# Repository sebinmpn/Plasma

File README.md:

Welcome to our plasma diagnostic devices page.

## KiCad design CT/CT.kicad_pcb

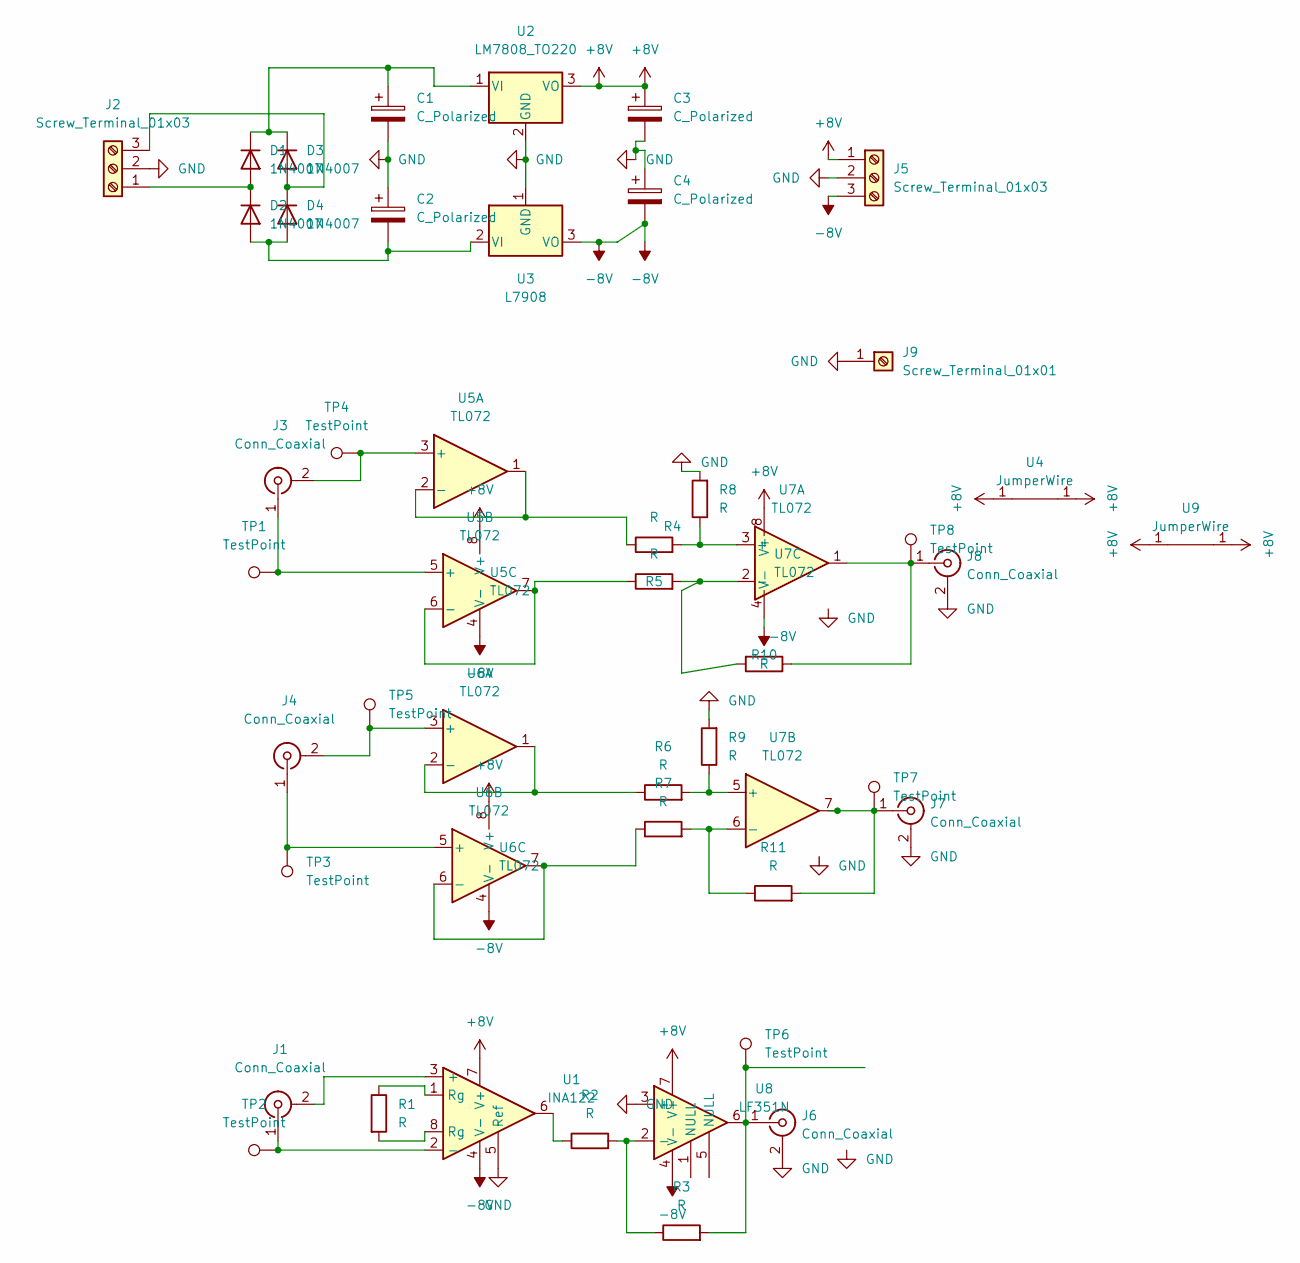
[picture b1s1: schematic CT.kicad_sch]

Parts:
C1, C2, C3, C4: C_Polarized; CP_Radial_D8.0mm_P3.50mm
D1, D2, D3, D4: 1N4007; D_DO-41_SOD81_P10.16mm_Horizontal
J1, J3, J4, J6, J7, J8: Conn_Coaxial; BNC_TEConnectivity_1478204_Vertical
J2, J5: Screw_Terminal_01x03; TerminalBlock_Phoenix_MKDS-1,5-3-5.08_1x03_P5.08mm_Horizont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
J9: Screw_Terminal_01x01; TestPoint_Loop_D2.54mm_Drill1.5mm_Beaded
R1, R2, R3, R4, R5, R6, R7, R8, R9: R; R_Axial_DIN0207_L6.3mm_D2.5mm_P7.62mm_Horizontal
R10, R11: R; R_0805_2012Metric_Pad1.20x1.40mm_HandSolder
TP1, TP2, TP3, TP4, TP5, TP6, TP7, TP8: TestPoint; PinHeader_1x01_P2.54mm_Vertical
U1: INA122; DIP-8_W7.62mm
U2: LM7808_TO220; TO-220-3_Vertical
U3: L7908; TO-220-3_Vertical
U4: JumperWire; JumperWire5
U5: TL072; DIP-8_W10.16mm_LongPads
U6, U7: TL072; DIP-8_W10.16mm
U8: LF351N; DIP-8_W10.16mm
U9: JumperWire; JumperWire6

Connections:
+8V: C3.1, J5.1, U1.7 (V+), U2.3 (VO), U4.1, U5.8 (V+), U6.8 (V+), U7.8 (V+), U8.7 (V+), U9.1
-8V: C4.2, J5.3, U1.4 (V-), U3.3 (VO), U5.4 (V-), U6.4 (V-), U7.4 (V-), U8.4 (V-)
GND: C1.2, C2.1, C3.2, C4.1, J2.2, J5.2, J6.2 (Ext), J7.2 (Ext), J8.2 (Ext), J9.1, R8.2, R9.2, U1.5 (Ref), U2.2 (GND), U3.1 (GND), U8.3 (+)
unnamed: C1.1, D1.1 (K), D3.1 (K), U2.1 (VI)
unnamed: C2.2, D2.2 (A), D4.2 (A), U3.2 (VI)
unnamed: D1.2 (A), D2.1 (K), J2.1
unnamed: D3.2 (A), D4.1 (K), J2.3
unnamed: J1.1 (In), TP2.1, U1.2 (-)
unnamed: J1.2 (Ext), U1.3 (+)
unnamed: J3.1 (In), TP1.1, U5.5 (+)
unnamed: J3.2 (Ext), TP4.1, U5.3 (+)
unnamed: J4.1 (In), TP3.1, U6.5 (+)
unnamed: J4.2 (Ext), TP5.1, U6.3 (+)
unnamed: J6.1 (In), R3.2, TP6.1, U8.6
unnamed: J7.1 (In), R11.2, TP7.1, U7.7
unnamed: J8.1 (In), R10.1, TP8.1, U7.1
unnamed: R1.1, U1.1 (Rg)
unnamed: R1.2, U1.8 (Rg)
unnamed: R2.1, U1.6
unnamed: R2.2, R3.1, U8.2 (-)
unnamed: R4.1, U5.1, U5.2 (-)
unnamed: R4.2, R8.1, U7.3 (+)
unnamed: R5.1, U5.6 (-), U5.7
unnamed: R6.1, U6.1, U6.2 (-)
unnamed: R6.2, R9.1, U7.5 (+)
unnamed: R7.1, U6.6 (-), U6.7
unnamed: R5.2, R10.2, U7.2 (-)
unnamed: R7.2, R11.1, U7.6 (-)

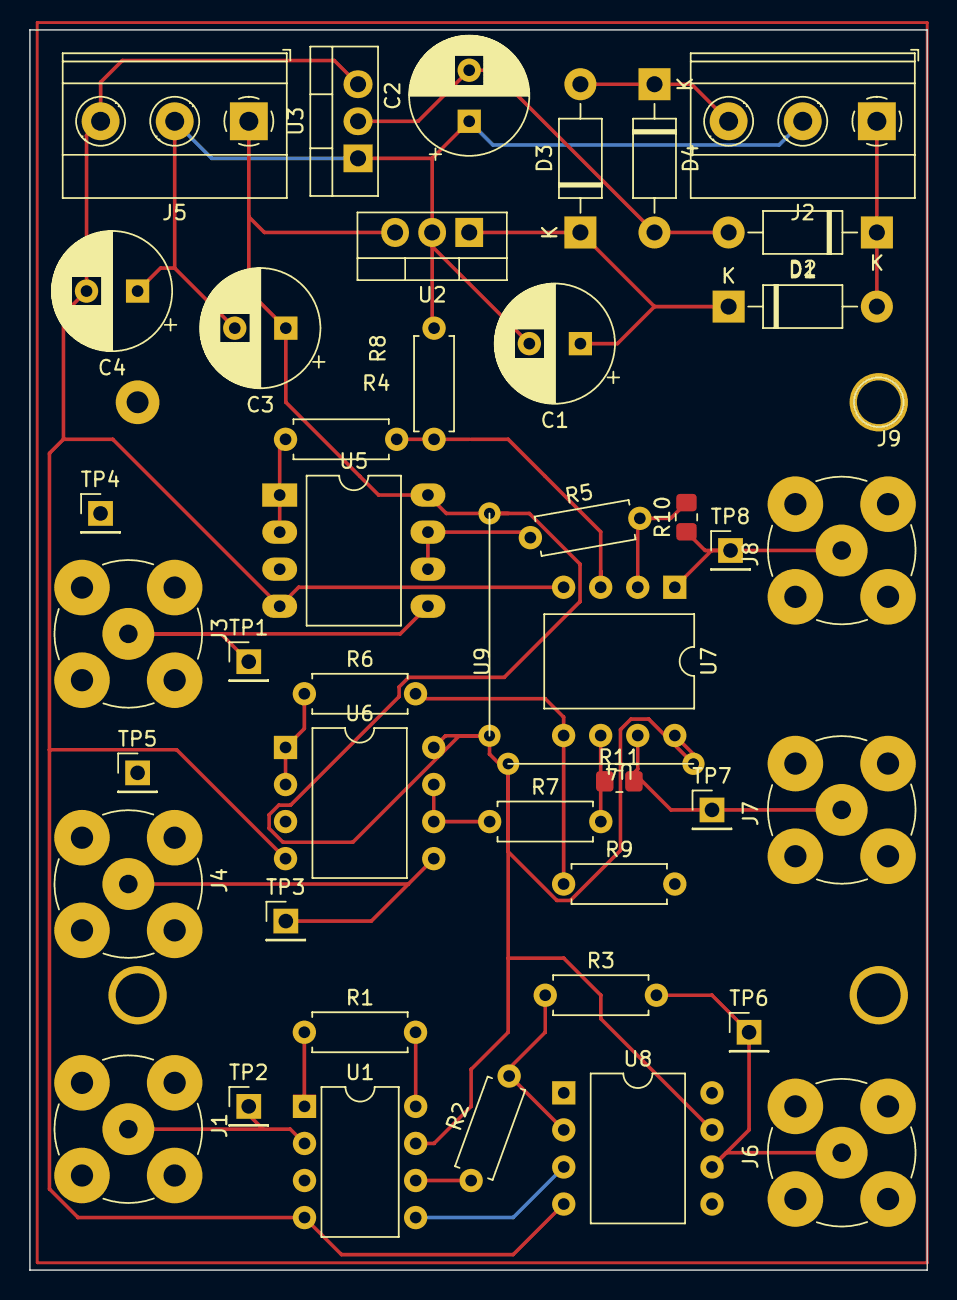
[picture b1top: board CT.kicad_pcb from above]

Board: 2 copper layers, 61.5 x 85.0 mm, 45 parts (0 on the bottom side), 28 nets.

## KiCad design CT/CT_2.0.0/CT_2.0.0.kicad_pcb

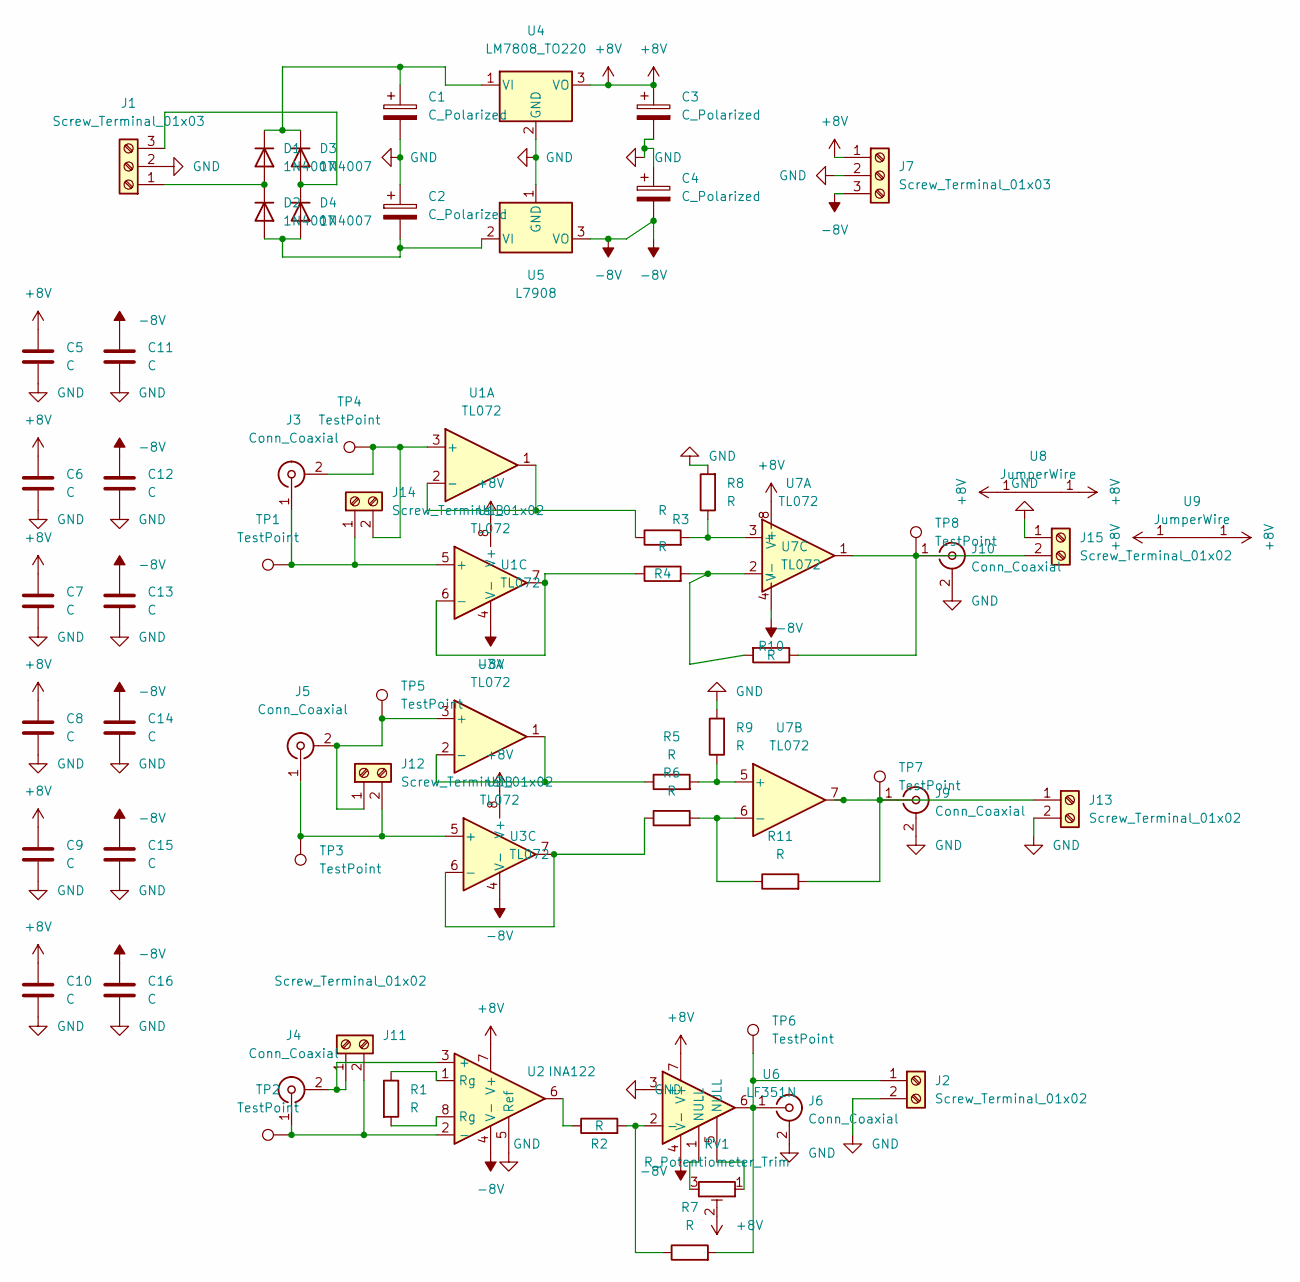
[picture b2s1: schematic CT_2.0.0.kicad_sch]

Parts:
C1, C2, C3, C4: C_Polarized; CP_Radial_D8.0mm_P3.50mm
C5, C6, C7, C8, C9, C10, C11, C12, C13, C14, C15, C16: C; CP_EIA-3528-21_Kemet-B_Pad1.50x2.35mm_HandSolder
D1, D2, D3, D4: 1N4007; D_DO-41_SOD81_P10.16mm_Horizontal
J1, J7: Screw_Terminal_01x03; TerminalBlock_Phoenix_MKDS-1,5-3-5.08_1x03_P5.08mm_Horizont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
J2, J11, J12, J13, J14, J15: Screw_Terminal_01x02; TerminalBlock_Phoenix_MKDS-1,5-2-5.08_1x02_P5.08mm_Horizont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
J3, J4, J5, J6, J9, J10: Conn_Coaxial; BNC_TEConnectivity_1478204_Vertical
R1, R2, R3, R4, R5, R6, R7, R8, R9: R; R_Axial_DIN0207_L6.3mm_D2.5mm_P7.62mm_Horizontal
R10, R11: R; R_0805_2012Metric_Pad1.20x1.40mm_HandSolder
RV1: R_Potentiometer_Trim; trimpot
TP1, TP2, TP3, TP4, TP5, TP6, TP7, TP8: TestPoint; PinHeader_1x01_P2.54mm_Vertical
U1: TL072; DIP-8_W10.16mm_LongPads
U2: INA122; DIP-8_W7.62mm
U3, U7: TL072; DIP-8_W10.16mm
U4: LM7808_TO220; TO-220-3_Vertical
U5: L7908; TO-220-3_Vertical
U6: LF351N; DIP-8_W10.16mm
U8: JumperWire; JumperWire5
U9: JumperWire; JumperWire6

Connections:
+8V: C3.1, C5.1, C6.1, C7.1, C8.1, C9.1, C10.1, J7.1, RV1.2, U1.8 (V+), U2.7 (V+), U3.8 (V+), U4.3 (VO), U6.7 (V+), U7.8 (V+), U8.1, U9.1
-8V: C4.2, C11.1, C12.1, C13.1, C14.1, C15.1, C16.1, J7.3, U1.4 (V-), U2.4 (V-), U3.4 (V-), U5.3 (VO), U6.4 (V-), U7.4 (V-)
GND: C1.2, C2.1, C3.2, C4.1, C5.2, C6.2, C7.2, C8.2, C9.2, C10.2, C11.2, C12.2, C13.2, C14.2, C15.2, C16.2, J1.2, J2.2, J6.2 (Ext), J7.2, J9.2 (Ext), J10.2 (Ext), J13.2, J15.1, R8.2, R9.2, U2.5 (Ref), U4.2 (GND), U5.1 (GND), U6.3 (+)
unnamed: C1.1, D1.1 (K), D3.1 (K), U4.1 (VI)
unnamed: C2.2, D2.2 (A), D4.2 (A), U5.2 (VI)
unnamed: D1.2 (A), D2.1 (K), J1.1
unnamed: D3.2 (A), D4.1 (K), J1.3
unnamed: J2.1, J6.1 (In), R7.2, TP6.1, U6.6
unnamed: J3.1 (In), J14.1, TP1.1, U1.5 (+)
unnamed: J3.2 (Ext), J14.2, TP4.1, U1.3 (+)
unnamed: J4.2 (Ext), J11.1, U2.3 (+)
unnamed: J4.1 (In), J11.2, TP2.1, U2.2 (-)
unnamed: J5.2 (Ext), J12.1, TP5.1, U3.3 (+)
unnamed: J5.1 (In), J12.2, TP3.1, U3.5 (+)
unnamed: J9.1 (In), J13.1, R11.2, TP7.1, U7.7
unnamed: J10.1 (In), J15.2, R10.1, TP8.1, U7.1
unnamed: R1.1, U2.1 (Rg)
unnamed: R1.2, U2.8 (Rg)
unnamed: R2.1, U2.6
unnamed: R2.2, R7.1, U6.2 (-)
unnamed: R3.1, U1.1, U1.2 (-)
unnamed: R3.2, R8.1, U7.3 (+)
unnamed: R4.1, U1.6 (-), U1.7
unnamed: R5.1, U3.1, U3.2 (-)
unnamed: R5.2, R9.1, U7.5 (+)
unnamed: R6.1, U3.6 (-), U3.7
unnamed: R4.2, R10.2, U7.2 (-)
unnamed: R6.2, R11.1, U7.6 (-)
unnamed: RV1.3, U6.1 (NULL)
unnamed: RV1.1, U6.5 (NULL)

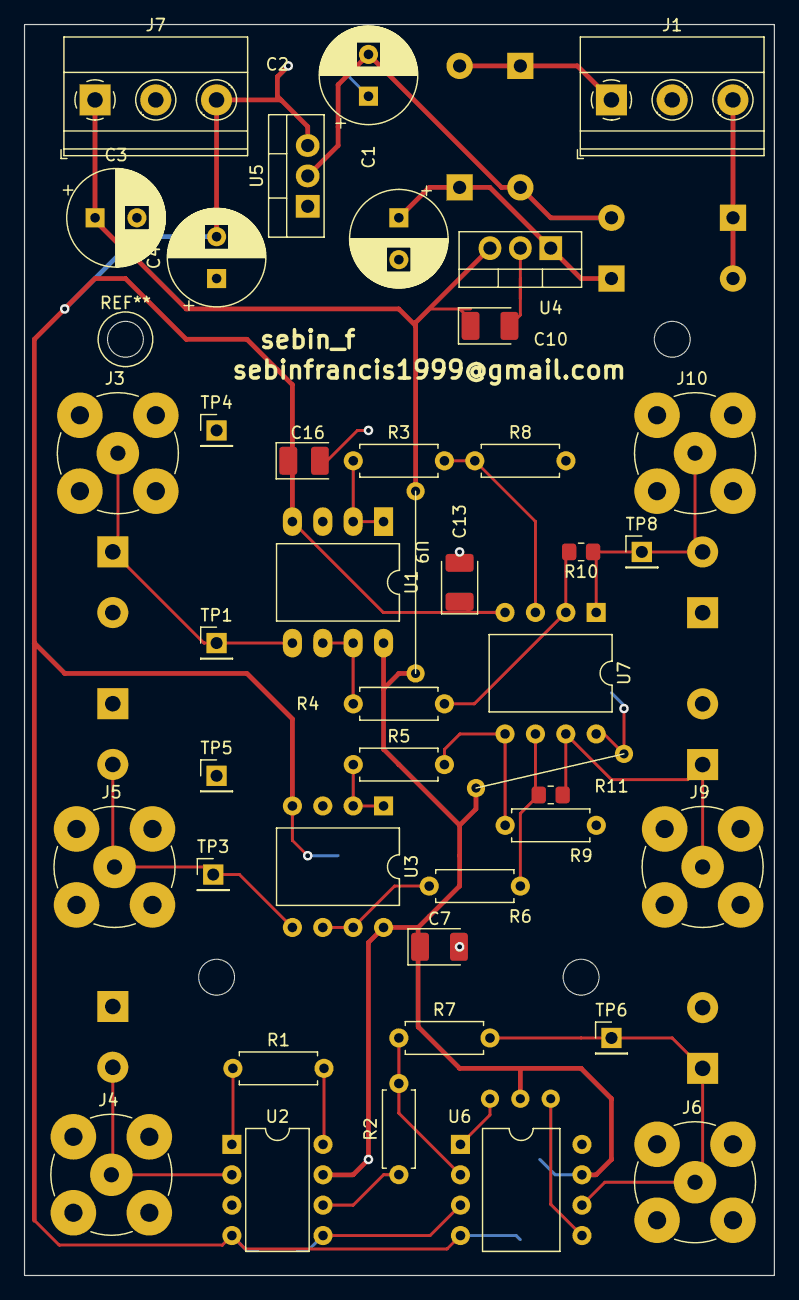
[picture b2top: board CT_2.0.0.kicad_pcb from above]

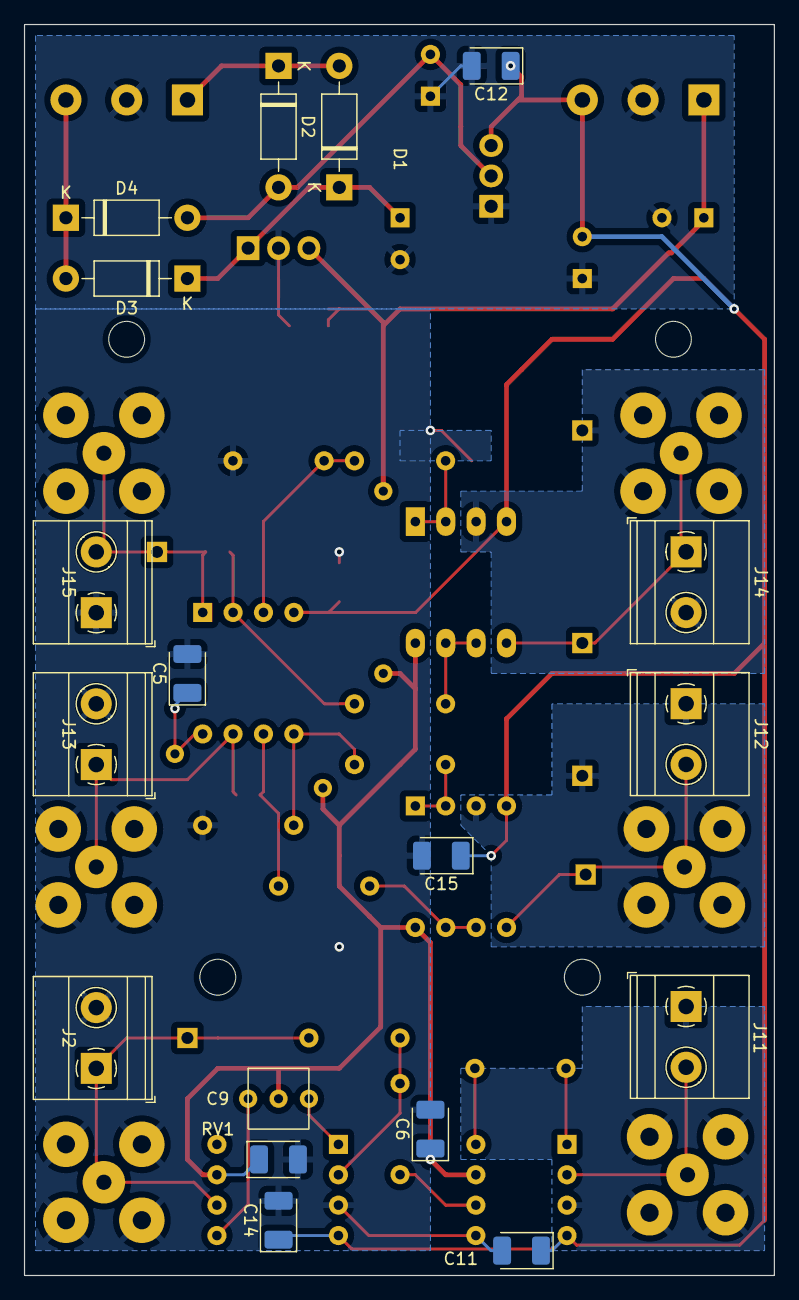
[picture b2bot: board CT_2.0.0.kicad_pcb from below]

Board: 2 copper layers, 62.7 x 104.6 mm, 60 parts (18 on the bottom side), 30 nets.

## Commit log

2025-05-07 adding
